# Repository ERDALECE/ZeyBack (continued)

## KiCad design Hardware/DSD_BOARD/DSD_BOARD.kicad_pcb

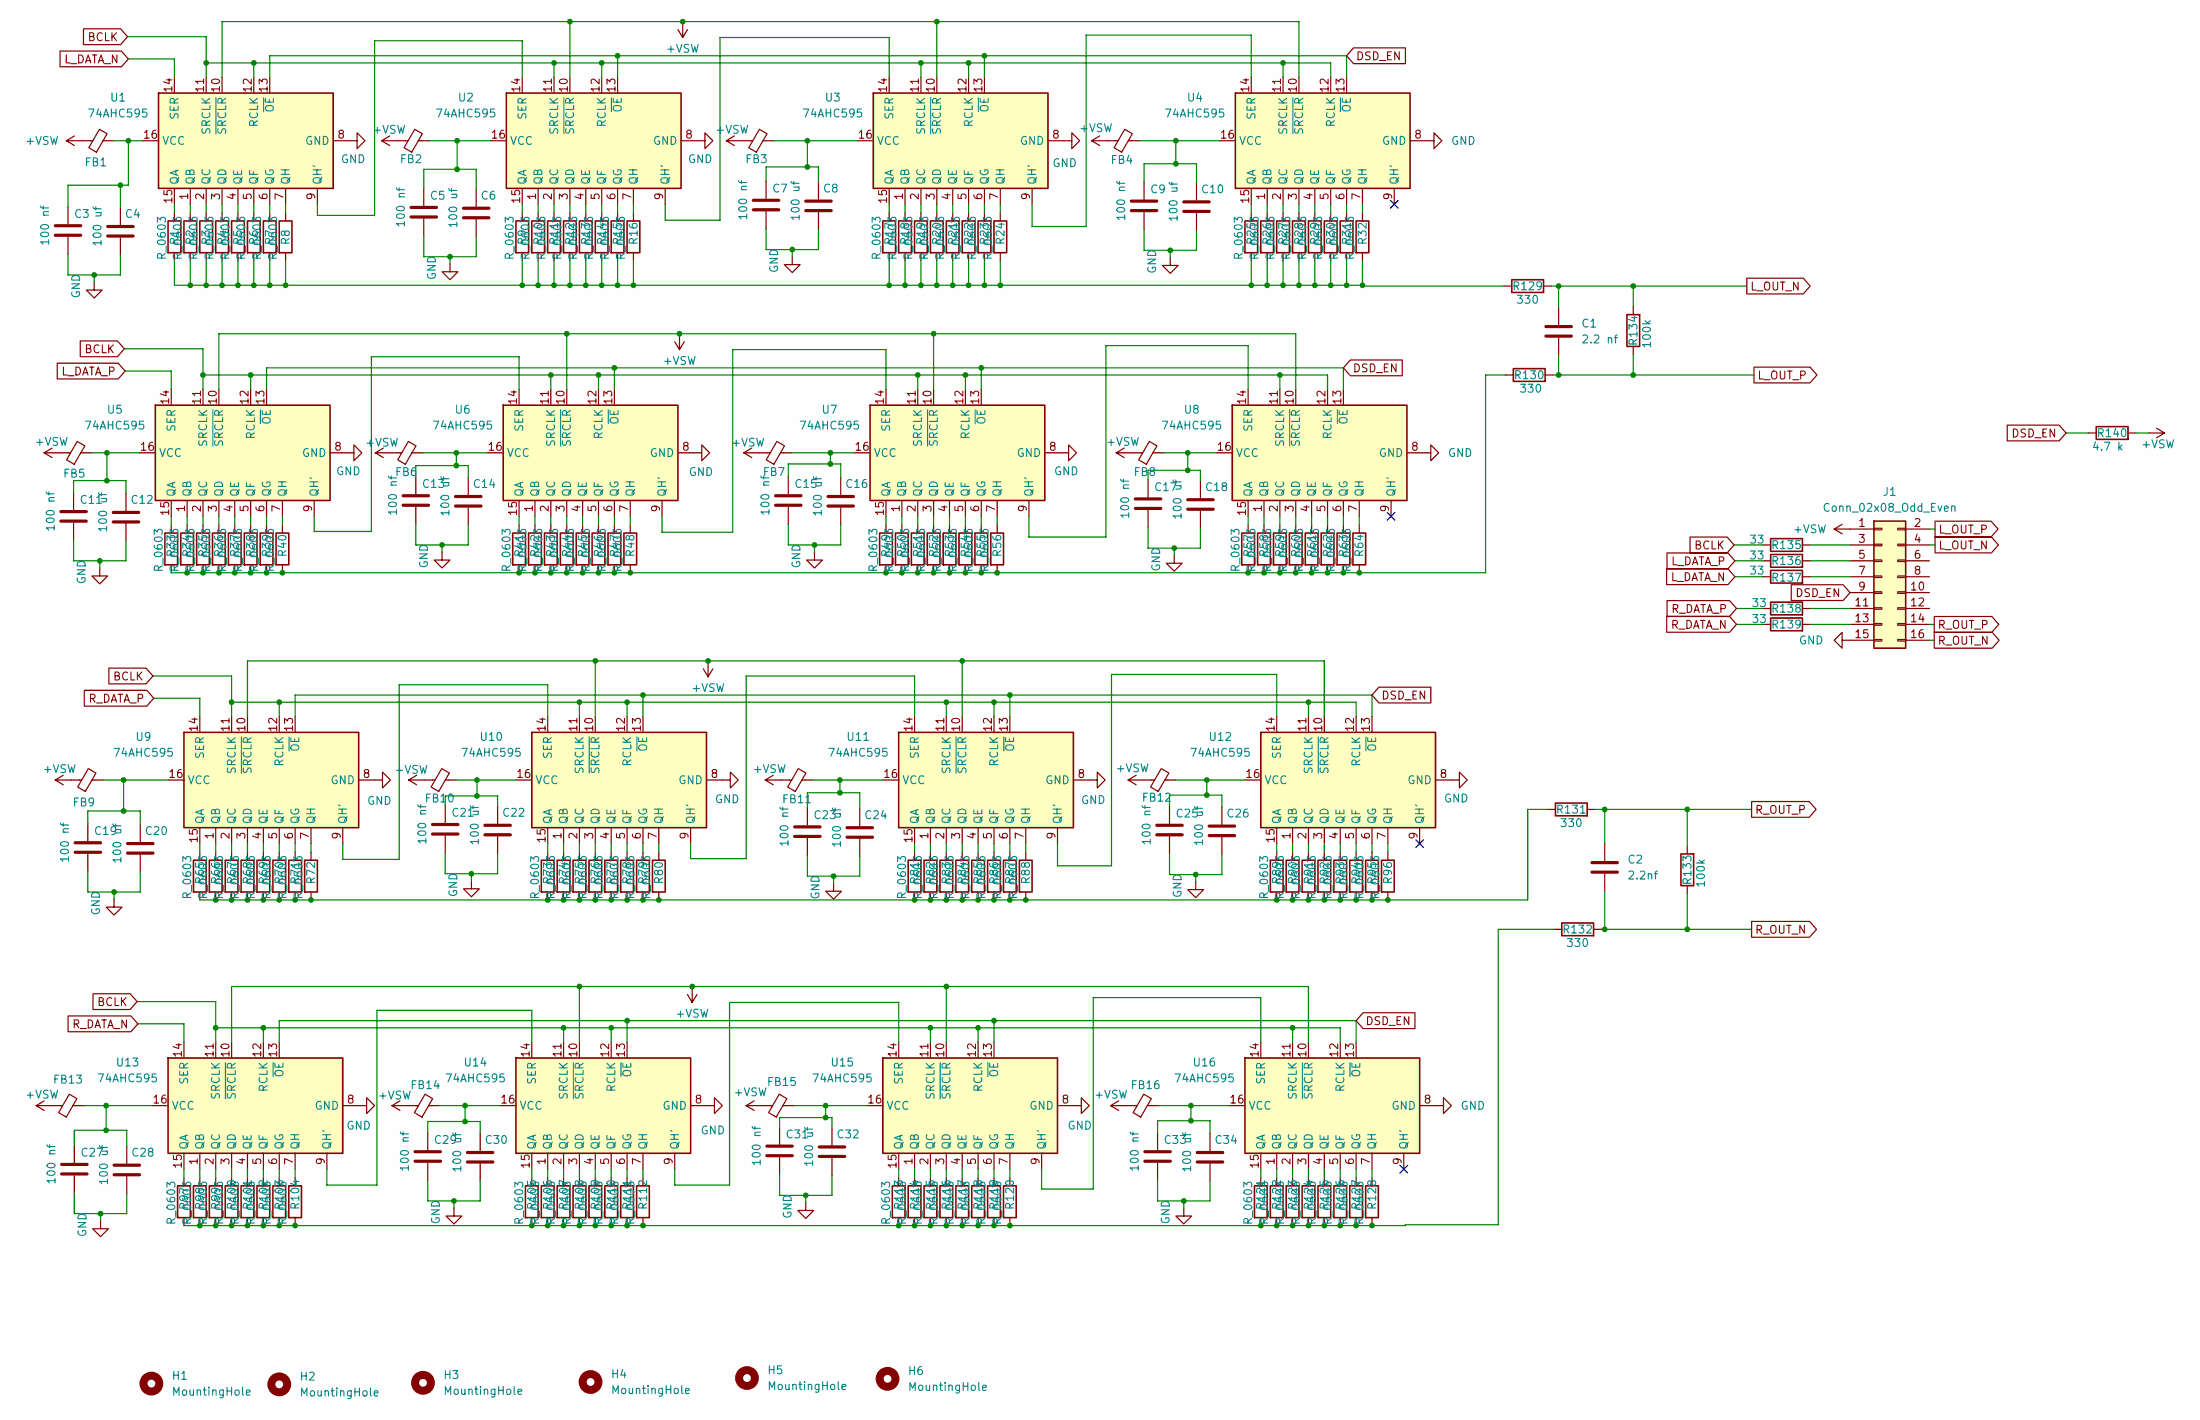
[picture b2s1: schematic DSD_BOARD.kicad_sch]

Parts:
C1: 2.2 nf; C_0603_1608Metric
C2: 2.2nf; C_0603_1608Metric
C3, C5, C7, C9, C11, C13, C15, C17, C19, C21, C23, C25, C27, C29, C31, C33: 100 nf; C_0603_1608Metric
C4, C6, C8, C10, C12, C14, C16, C18, C20, C22, C24, C26, C28, C30, C32, C34: 100 uf; C_1210_3225Metric_Pad1.33x2.70mm
FB1, FB2, FB3, FB4, FB5, FB6, FB7, FB8, FB9, FB10, FB11, FB12, FB13, FB14, FB15, FB16: bead; R_0603_1608Metric
H1, H2, H3, H4, H5, H6: MountingHole; MountingHole_3.2mm_M3
J1: Conn_02x08_Odd_Even; PinHeader_2x08_P2.54mm_Vertical
R1, R2, R3, R4, R5, R6, R7, R8, R9, R10, R11, R12, R13, R14, R15, R16, R17, R18, R19, R20, R21, R22, R23, R24, R25, R26, R27, R28, R29, R30, R31, R32, R33, R34, R35, R36, R37, R38, R39, R40, R41, R42, R43, R44, R45, R46, R47, R48, R49, R50, R51, R52, R53, R54, R55, R56, R57, R58, R59, R60, R61, R62, R63, R64, R65, R66, R67, R68, R69, R70, R71, R72, R73, R74, R75, R76, R77, R78, R79, R80, R81, R82, R83, R84, R85, R86, R87, R88, R89, R90, R91, R92, R93, R94, R95, R96, R97, R98, R99, R100, R101, R102, R103, R104, R105, R106, R107, R108, R109, R110, R111, R112, R113, R114, R115, R116, R117, R118, R119, R120, R121, R122, R123, R124, R125, R126, R127, R128: R_0603; R_0603_1608Metric
R129, R130, R131, R132: 330; R_0603_1608Metric
R133, R134: 100k; R_0603_1608Metric
R135, R136, R137, R138, R139: 33; R_0603_1608Metric
R140: 4.7 k; R_0603_1608Metric
U1, U2, U3, U4, U5, U6, U7, U8, U9, U10, U11, U12, U13, U14, U15, U16: 74AHC595; TSSOP-16_4.4x5mm_P0.65mm

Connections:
+VSW: FB1.1, FB2.1, FB3.1, FB4.1, FB5.1, FB6.1, FB7.1, FB8.1, FB9.1, FB10.1, FB11.1, FB12.1, FB13.1, FB14.1, FB15.1, FB16.1, J1.1, R140.2, U1.10 (~SRCLR), U2.10 (~SRCLR), U3.10 (~SRCLR), U4.10 (~SRCLR), U5.10 (~SRCLR), U6.10 (~SRCLR), U7.10 (~SRCLR), U8.10 (~SRCLR), U9.10 (~SRCLR), U10.10 (~SRCLR), U11.10 (~SRCLR), U12.10 (~SRCLR), U13.10 (~SRCLR), U14.10 (~SRCLR), U15.10 (~SRCLR), U16.10 (~SRCLR)
BCLK: R135.1, U1.11 (SRCLK), U1.12 (RCLK), U2.11 (SRCLK), U2.12 (RCLK), U3.11 (SRCLK), U3.12 (RCLK), U4.11 (SRCLK), U4.12 (RCLK), U5.11 (SRCLK), U5.12 (RCLK), U6.11 (SRCLK), U6.12 (RCLK), U7.11 (SRCLK), U7.12 (RCLK), U8.11 (SRCLK), U8.12 (RCLK), U9.11 (SRCLK), U9.12 (RCLK), U10.11 (SRCLK), U10.12 (RCLK), U11.11 (SRCLK), U11.12 (RCLK), U12.11 (SRCLK), U12.12 (RCLK), U13.11 (SRCLK), U13.12 (RCLK), U14.11 (SRCLK), U14.12 (RCLK), U15.11 (SRCLK), U15.12 (RCLK), U16.11 (SRCLK), U16.12 (RCLK)
DSD_EN: J1.9, R140.1, U1.13 (~OE), U2.13 (~OE), U3.13 (~OE), U4.13 (~OE), U5.13 (~OE), U6.13 (~OE), U7.13 (~OE), U8.13 (~OE), U9.13 (~OE), U10.13 (~OE), U11.13 (~OE), U12.13 (~OE), U13.13 (~OE), U14.13 (~OE), U15.13 (~OE), U16.13 (~OE)
GND: C3.2, C4.2, C5.2, C6.2, C7.2, C8.2, C9.2, C10.2, C11.2, C12.2, C13.2, C14.2, C15.2, C16.2, C17.2, C18.2, C19.2, C20.2, C21.2, C22.2, C23.2, C24.2, C25.2, C26.2, C27.2, C28.2, C29.2, C30.2, C31.2, C32.2, C33.2, C34.2, J1.15, U1.8 (GND), U2.8 (GND), U3.8 (GND), U4.8 (GND), U5.8 (GND), U6.8 (GND), U7.8 (GND), U8.8 (GND), U9.8 (GND), U10.8 (GND), U11.8 (GND), U12.8 (GND), U13.8 (GND), U14.8 (GND), U15.8 (GND), U16.8 (GND)
L_DATA_N: R137.1, U1.14 (SER)
L_DATA_P: R136.1, U5.14 (SER)
L_OUT_N: C1.1, J1.4, R129.2, R134.2
L_OUT_P: C1.2, J1.2, R130.2, R134.1
unnamed: J1.3, R135.2
unnamed: J1.5, R136.2
unnamed: J1.7, R137.2
unnamed: J1.11, R138.2
unnamed: J1.13, R139.2
unnamed: R1.2, R2.2, R3.2, R4.2, R5.2, R6.2, R7.2, R8.2, R9.2, R10.2, R11.2, R12.2, R13.2, R14.2, R15.2, R16.2, R17.2, R18.2, R19.2, R20.2, R21.2, R22.2, R23.2, R24.2, R25.2, R26.2, R27.2, R28.2, R29.2, R30.2, R31.2, R32.2, R129.1
unnamed: R97.2, R98.2, R99.2, R100.2, R101.2, R102.2, R103.2, R104.2, R105.2, R106.2, R107.2, R108.2, R109.2, R110.2, R111.2, R112.2, R113.2, R114.2, R115.2, R116.2, R117.2, R118.2, R119.2, R120.2, R121.2, R122.2, R123.2, R124.2, R125.2, R126.2, R127.2, R128.2, R132.1
unnamed: R33.2, R34.2, R35.2, R36.2, R37.2, R38.2, R39.2, R40.2, R41.2, R42.2, R43.2, R44.2, R45.2, R46.2, R47.2, R48.2, R49.2, R50.2, R51.2, R52.2, R53.2, R54.2, R55.2, R56.2, R57.2, R58.2, R59.2, R60.2, R61.2, R62.2, R63.2, R64.2, R130.1
unnamed: R65.2, R66.2, R67.2, R68.2, R69.2, R70.2, R71.2, R72.2, R73.2, R74.2, R75.2, R76.2, R77.2, R78.2, R79.2, R80.2, R81.2, R82.2, R83.2, R84.2, R85.2, R86.2, R87.2, R88.2, R89.2, R90.2, R91.2, R92.2, R93.2, R94.2, R95.2, R96.2, R131.1
unnamed: R1.1, U1.15 (QA)
unnamed: R2.1, U1.1 (QB)
unnamed: R3.1, U1.2 (QC)
unnamed: R4.1, U1.3 (QD)
unnamed: R5.1, U1.4 (QE)
unnamed: R6.1, U1.5 (QF)
unnamed: R7.1, U1.6 (QG)
unnamed: U1.9 (QH'), U2.14 (SER)
unnamed: R8.1, U1.7 (QH)
unnamed: C3.1, C4.1, FB1.2, U1.16 (VCC)
unnamed: R9.1, U2.15 (QA)
unnamed: R10.1, U2.1 (QB)
unnamed: R11.1, U2.2 (QC)
unnamed: R12.1, U2.3 (QD)
unnamed: R13.1, U2.4 (QE)
unnamed: R14.1, U2.5 (QF)
unnamed: R15.1, U2.6 (QG)
unnamed: U2.9 (QH'), U3.14 (SER)
unnamed: R16.1, U2.7 (QH)
unnamed: C5.1, C6.1, FB2.2, U2.16 (VCC)
unnamed: R17.1, U3.15 (QA)
unnamed: R18.1, U3.1 (QB)
unnamed: R19.1, U3.2 (QC)
unnamed: R20.1, U3.3 (QD)
unnamed: R21.1, U3.4 (QE)
unnamed: R22.1, U3.5 (QF)
unnamed: R23.1, U3.6 (QG)
unnamed: U3.9 (QH'), U4.14 (SER)
unnamed: R24.1, U3.7 (QH)
unnamed: C7.1, C8.1, FB3.2, U3.16 (VCC)
unnamed: R25.1, U4.15 (QA)
unnamed: R26.1, U4.1 (QB)
unnamed: R27.1, U4.2 (QC)
unnamed: R28.1, U4.3 (QD)
unnamed: R29.1, U4.4 (QE)
unnamed: R30.1, U4.5 (QF)
unnamed: R31.1, U4.6 (QG)
unnamed: R32.1, U4.7 (QH)
unnamed: C9.1, C10.1, FB4.2, U4.16 (VCC)
unnamed: R33.1, U5.15 (QA)
unnamed: R34.1, U5.1 (QB)
unnamed: R35.1, U5.2 (QC)
unnamed: R36.1, U5.3 (QD)
unnamed: R37.1, U5.4 (QE)
unnamed: R38.1, U5.5 (QF)
unnamed: R39.1, U5.6 (QG)
unnamed: U5.9 (QH'), U6.14 (SER)
unnamed: R40.1, U5.7 (QH)
unnamed: C11.1, C12.1, FB5.2, U5.16 (VCC)
unnamed: R41.1, U6.15 (QA)
unnamed: R42.1, U6.1 (QB)
unnamed: R43.1, U6.2 (QC)
unnamed: R44.1, U6.3 (QD)
unnamed: R45.1, U6.4 (QE)
unnamed: R46.1, U6.5 (QF)
unnamed: R47.1, U6.6 (QG)
unnamed: U6.9 (QH'), U7.14 (SER)
unnamed: R48.1, U6.7 (QH)
unnamed: C13.1, C14.1, FB6.2, U6.16 (VCC)
unnamed: R49.1, U7.15 (QA)
unnamed: R50.1, U7.1 (QB)
unnamed: R51.1, U7.2 (QC)
unnamed: R52.1, U7.3 (QD)
unnamed: R53.1, U7.4 (QE)
unnamed: R54.1, U7.5 (QF)
unnamed: R55.1, U7.6 (QG)
unnamed: U7.9 (QH'), U8.14 (SER)
unnamed: R56.1, U7.7 (QH)
unnamed: C15.1, C16.1, FB7.2, U7.16 (VCC)
unnamed: R57.1, U8.15 (QA)
unnamed: R58.1, U8.1 (QB)
unnamed: R59.1, U8.2 (QC)
unnamed: R60.1, U8.3 (QD)
unnamed: R61.1, U8.4 (QE)
unnamed: R62.1, U8.5 (QF)
unnamed: R63.1, U8.6 (QG)
unnamed: R64.1, U8.7 (QH)
unnamed: C17.1, C18.1, FB8.2, U8.16 (VCC)
unnamed: R65.1, U9.15 (QA)
unnamed: R66.1, U9.1 (QB)
unnamed: R67.1, U9.2 (QC)
unnamed: R68.1, U9.3 (QD)
unnamed: R69.1, U9.4 (QE)
unnamed: R70.1, U9.5 (QF)
unnamed: R71.1, U9.6 (QG)
unnamed: R72.1, U9.7 (QH)
unnamed: C19.1, C20.1, FB9.2, U9.16 (VCC)
unnamed: R73.1, U10.15 (QA)
unnamed: R74.1, U10.1 (QB)
unnamed: R75.1, U10.2 (QC)
unnamed: R76.1, U10.3 (QD)
unnamed: R77.1, U10.4 (QE)
unnamed: R78.1, U10.5 (QF)
unnamed: R79.1, U10.6 (QG)
unnamed: U10.9 (QH'), U11.14 (SER)
unnamed: R80.1, U10.7 (QH)
unnamed: U9.9 (QH'), U10.14 (SER)
unnamed: C21.1, C22.1, FB10.2, U10.16 (VCC)
unnamed: R81.1, U11.15 (QA)
unnamed: R82.1, U11.1 (QB)
unnamed: R83.1, U11.2 (QC)
unnamed: R84.1, U11.3 (QD)
unnamed: R85.1, U11.4 (QE)
unnamed: R86.1, U11.5 (QF)
unnamed: R87.1, U11.6 (QG)
unnamed: U11.9 (QH'), U12.14 (SER)
unnamed: R88.1, U11.7 (QH)
unnamed: C23.1, C24.1, FB11.2, U11.16 (VCC)
unnamed: R89.1, U12.15 (QA)
unnamed: R90.1, U12.1 (QB)
unnamed: R91.1, U12.2 (QC)
unnamed: R92.1, U12.3 (QD)
unnamed: R93.1, U12.4 (QE)
unnamed: R94.1, U12.5 (QF)
unnamed: R95.1, U12.6 (QG)
unnamed: R96.1, U12.7 (QH)
unnamed: C25.1, C26.1, FB12.2, U12.16 (VCC)
unnamed: R97.1, U13.15 (QA)
unnamed: R98.1, U13.1 (QB)
unnamed: R99.1, U13.2 (QC)
unnamed: R100.1, U13.3 (QD)
unnamed: R101.1, U13.4 (QE)
unnamed: R102.1, U13.5 (QF)
unnamed: R103.1, U13.6 (QG)
unnamed: U13.9 (QH'), U14.14 (SER)
unnamed: R104.1, U13.7 (QH)
unnamed: C27.1, C28.1, FB13.2, U13.16 (VCC)
unnamed: R105.1, U14.15 (QA)
unnamed: R106.1, U14.1 (QB)
unnamed: R107.1, U14.2 (QC)
unnamed: R108.1, U14.3 (QD)
unnamed: R109.1, U14.4 (QE)
unnamed: R110.1, U14.5 (QF)
unnamed: R111.1, U14.6 (QG)
unnamed: U14.9 (QH'), U15.14 (SER)
unnamed: R112.1, U14.7 (QH)
unnamed: C29.1, C30.1, FB14.2, U14.16 (VCC)
unnamed: R113.1, U15.15 (QA)
unnamed: R114.1, U15.1 (QB)
unnamed: R115.1, U15.2 (QC)
unnamed: R116.1, U15.3 (QD)
unnamed: R117.1, U15.4 (QE)
unnamed: R118.1, U15.5 (QF)
unnamed: R119.1, U15.6 (QG)
unnamed: U15.9 (QH'), U16.14 (SER)
unnamed: R120.1, U15.7 (QH)
unnamed: C31.1, C32.1, FB15.2, U15.16 (VCC)
unnamed: R121.1, U16.15 (QA)
unnamed: R122.1, U16.1 (QB)
unnamed: R123.1, U16.2 (QC)
unnamed: R124.1, U16.3 (QD)
unnamed: R125.1, U16.4 (QE)
unnamed: R126.1, U16.5 (QF)
unnamed: R127.1, U16.6 (QG)
unnamed: R128.1, U16.7 (QH)
unnamed: C33.1, C34.1, FB16.2, U16.16 (VCC)
R_DATA_N: R139.1, U13.14 (SER)
R_DATA_P: R138.1, U9.14 (SER)
R_OUT_N: C2.2, J1.16, R132.2, R133.1
R_OUT_P: C2.1, J1.14, R131.2, R133.2

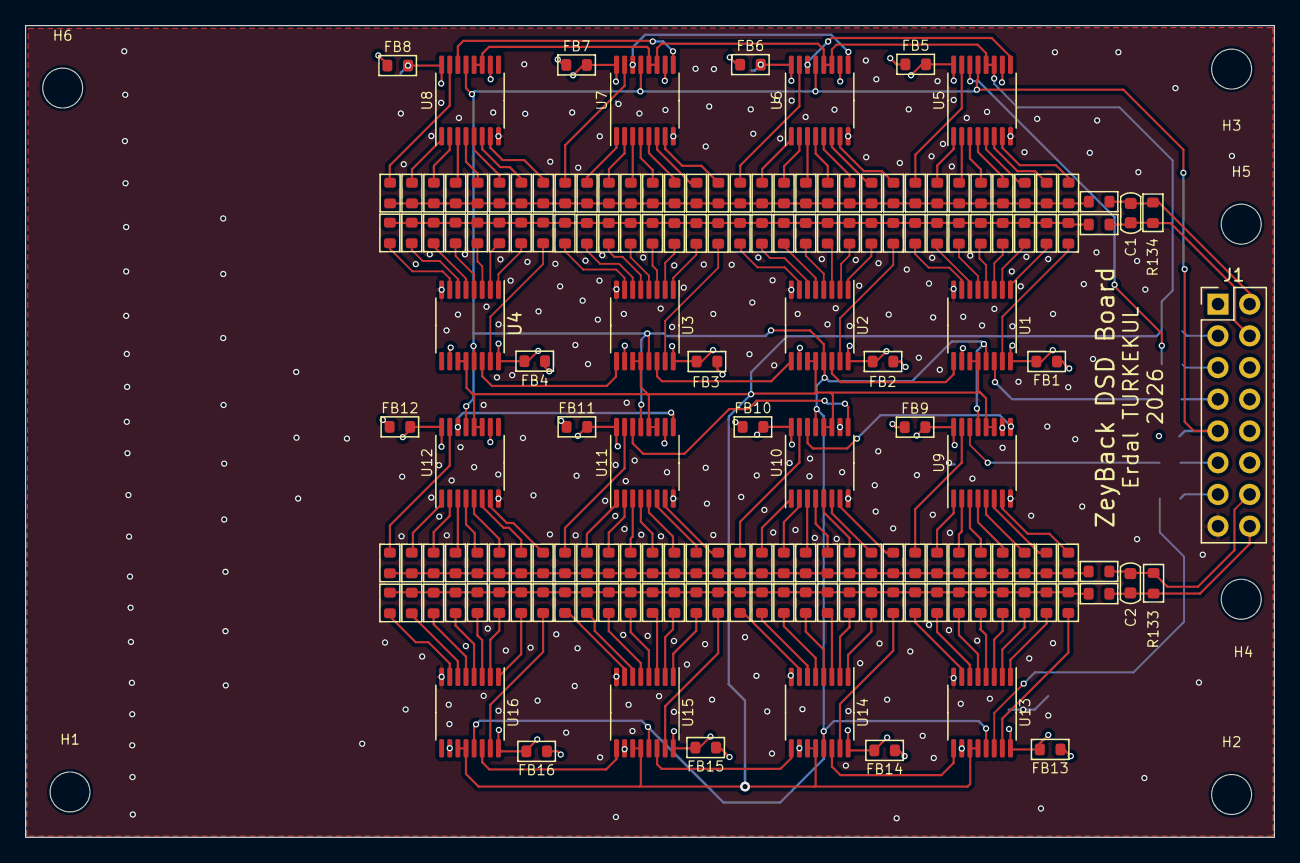
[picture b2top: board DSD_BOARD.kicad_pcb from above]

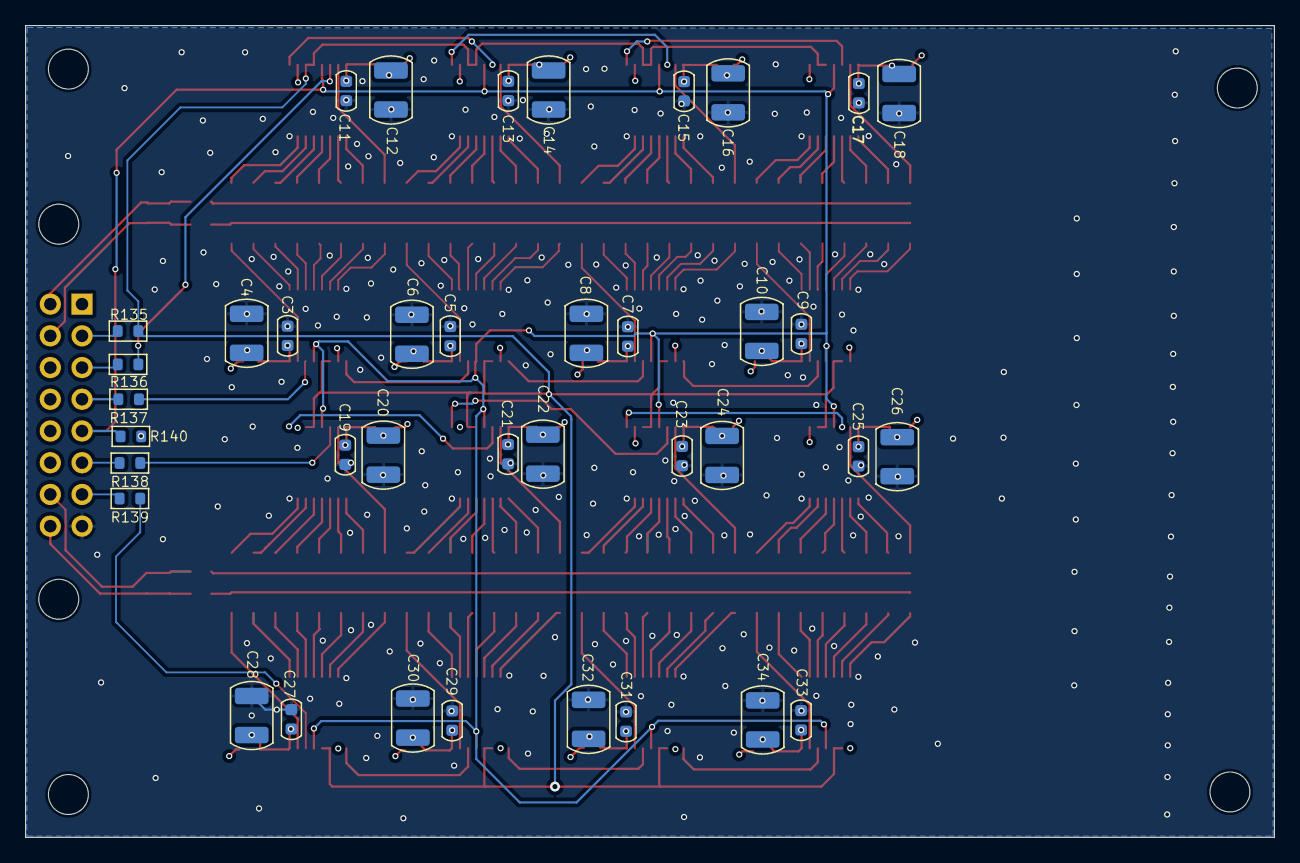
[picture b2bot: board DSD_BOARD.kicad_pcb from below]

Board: 4 copper layers, 100.0 x 65.0 mm, 213 parts (38 on the bottom side), 177 nets.

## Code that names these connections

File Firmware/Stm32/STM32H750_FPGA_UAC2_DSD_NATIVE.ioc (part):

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Mcu.Name=STM32H750XBHx
Mcu.Package=TFBGA240
Mcu.UserName=STM32H750XBHx
PA0.GPIOParameters=GPIO_Speed,PinState,GPIO_PuPd,GPIO_Label
PA0.GPIO_Label=USB_RST
PA0.GPIO_PuPd=GPIO_NOPULL
PA0.GPIO_Speed=GPIO_SPEED_FREQ_MEDIUM
PA0.PinState=GPIO_PIN_SET
PA0.Signal=GPIO_Output
PA1.GPIOParameters=GPIO_Label
PA1.GPIO_Label=LED2
PA1.Signal=GPIO_Output
PA10.GPIOParameters=GPIO_Speed,PinState,GPIO_Label
PA10.GPIO_Label=RST_SI
PA10.GPIO_Speed=GPIO_SPEED_FREQ_MEDIUM
PA10.PinState=GPIO_PIN_SET
PA10.Signal=GPIO_Output
PA12.GPIOParameters=GPIO_Label
PA12.GPIO_Label=OLED_CLK
PA12.Mode=Simplex_Bidirectional_Master
PA12.Signal=SPI2_SCK
PA15\ (JTDI).Signal=S_TIM2_CH1_ETR
PA3.Mode=Device_HS
PA3.Signal=USB_OTG_HS_ULPI_D0
PA4.GPIOParameters=GPIO_Label
PA4.GPIO_Label=LED1
PA4.Signal=GPIO_Output
PA5.Mode=Device_HS
PA5.Signal=USB_OTG_HS_ULPI_CK
PA8.Mode=Clock-out-1
PA8.Signal=RCC_MCO_1
PA9.GPIOParameters=GPIO_PuPd,GPIO_Label
PA9.GPIO_Label=STM32_SYNC
PA9.GPIO_PuPd=GPIO_PULLUP
PA9.Signal=GPIO_Input
PB0.Mode=Device_HS
PB0.Signal=USB_OTG_HS_ULPI_D1
PB1.Mode=Device_HS
PB1.Signal=USB_OTG_HS_ULPI_D2
PB10.GPIOParameters=PinAttribute
PB10.Mode=Device_HS
PB10.PinAttribute=Free
PB10.Signal=USB_OTG_HS_ULPI_D3
PB11.GPIOParameters=PinAttribute
PB11.Mode=Device_HS
PB11.PinAttribute=Free
PB11.Signal=USB_OTG_HS_ULPI_D4
PB12.Mode=Device_HS
PB12.Signal=USB_OTG_HS_ULPI_D5
PB13.Mode=Device_HS
PB13.Signal=USB_OTG_HS_ULPI_D6
PB14.GPIOParameters=GPIO_Label
PB14.GPIO_Label=OLED_CS
PB14.Signal=GPIO_Output
PB15.GPIOParameters=GPIO_Label
PB15.GPIO_Label=OLED_DATA
PB15.Mode=Simplex_Bidirectional_Master
PB15.Signal=SPI2_MOSI
PB5.Mode=Device_HS
PB5.Signal=USB_OTG_HS_ULPI_D7
PB6.Mode=I2C
PB6.Signal=I2C1_SCL
PB7.Mode=I2C
PB7.Signal=I2C1_SDA
PC0.GPIOParameters=PinAttribute
PC0.Mode=Device_HS
PC0.PinAttribute=Free
PC0.Signal=USB_OTG_HS_ULPI_STP
PC10.Mode=Asynchronous
PC10.Signal=UART4_TX
PC11.Mode=Asynchronous
PC11.Signal=UART4_RX
PC15-OSC32_OUT\ (OSC32_OUT).GPIOParameters=GPIO_Label
PC15-OSC32_OUT\ (OSC32_OUT).GPIO_Label=RSTB
PC15-OSC32_OUT\ (OSC32_OUT).Signal=GPIO_Output
PC3.GPIOParameters=PinAttribute
PC3.Mode=Device_HS
PC3.PinAttribute=Free
PC3.Signal=USB_OTG_HS_ULPI_NXT
PC4.GPIOParameters=GPIO_Label
PC4.GPIO_Label=LED3
PC4.Signal=GPIO_Output
PC5.GPIOParameters=GPIO_Label
PC5.GPIO_Label=LED4
PC5.Signal=GPIO_Output
PC8.GPIOParameters=GPIO_PuPd,GPIO_Label
PC8.GPIO_Label=STM32_EN
PC8.GPIO_PuPd=GPIO_PULLUP
PC8.Signal=GPIO_Output
PC9.GPIOParameters=GPIO_PuPd,GPIO_Label
PC9.GPIO_Label=STM32_REQ
PC9.GPIO_PuPd=GPIO_PULLUP
PC9.Signal=GPIO_Input
PD0.Signal=FMC_D2_DA2
PD1.Signal=FMC_D3_DA3
PD10.Signal=FMC_D15_DA15
PD14.Signal=FMC_D0_DA0
PD15.Signal=FMC_D1_DA1
PD2.GPIOParameters=GPIO_Label
PD2.GPIO_Label=DSP
PD2.Signal=GPIO_Output
PD3.GPIOParameters=GPIO_Label
PD3.GPIO_Label=DSD_EN
PD3.Signal=GPIO_Output
PD4.GPIOParameters=GPIO_PuPd
PD4.GPIO_PuPd=GPIO_PULLUP
PD4.Signal=FMC_NOE
PD5.GPIOParameters=GPIO_PuPd
PD5.GPIO_PuPd=GPIO_PULLUP
PD5.Signal=FMC_NWE
PD6.GPIOParameters=GPIO_PuPd
PD6.GPIO_PuPd=GPIO_PULLUP
PD6.Signal=FMC_NWAIT
PD7.Mode=NorPsramChipSelect1_1
PD7.Signal=FMC_NE1
PD8.Signal=FMC_D13_DA13
PD9.Signal=FMC_D14_DA14
PE10.GPIOParameters=PinAttribute
PE10.PinAttribute=Free
PE10.Signal=FMC_D7_DA7
PE11.GPIOParameters=PinAttribute
PE11.PinAttribute=Free
PE11.Signal=FMC_D8_DA8
PE12.Signal=FMC_D9_DA9
PE13.Signal=FMC_D10_DA10
PE14.Signal=FMC_D11_DA11
PE15.Signal=FMC_D12_DA12
PE2.Mode=Full_Duplex_Master
PE2.Signal=SPI4_SCK
PE4.GPIOParameters=GPIO_Label
PE4.GPIO_Label=CS8416_CSB
PE4.Signal=GPIO_Output
PE5.Mode=Full_Duplex_Master
PE5.Signal=SPI4_MISO
PE6.Mode=Full_Duplex_Master
PE6.Signal=SPI4_MOSI
PE7.Signal=FMC_D4_DA4
PE8.Signal=FMC_D5_DA5
PE9.GPIOParameters=PinAttribute
PE9.PinAttribute=Free
PE9.Signal=FMC_D6_DA6
PF0.GPIOParameters=PinAttribute
PF0.PinAttribute=Free
PF0.Signal=FMC_A0
PF1.GPIOParameters=PinAttribute
PF1.PinAttribute=Free
PF1.Signal=FMC_A1
PF15.GPIOParameters=GPIO_Label
PF15.GPIO_Label=IR
PF15.Signal=GPIO_Input
PG2.GPIOParameters=GPIO_PuPd,GPIO_Label
PG2.GPIO_Label=SEL0
PG2.GPIO_PuPd=GPIO_PULLDOWN
PG2.Signal=GPIO_Output
PG3.GPIOParameters=GPIO_PuPd,GPIO_Label
PG3.GPIO_Label=SEL1
PG3.GPIO_PuPd=GPIO_PULLDOWN
PG3.Signal=GPIO_Output
PG4.GPIOParameters=GPIO_PuPd,GPIO_Label
PG4.GPIO_Label=SEL2
PG4.GPIO_PuPd=GPIO_PULLDOWN
PG4.Signal=GPIO_Output
PG5.GPIOParameters=GPIO_PuPd,GPIO_Label
PG5.GPIO_Label=SEL3
PG5.GPIO_PuPd=GPIO_PULLDOWN
PG5.Signal=GPIO_Output
PG6.GPIOParameters=GPIO_Label
PG6.GPIO_Label=RCLK_ON
PG6.Signal=GPIO_Output
PG7.GPIOParameters=GPIO_Label
PG7.GPIO_Label=MUTE
PG7.Signal=GPIO_Output
PH0-OSC_IN\ (PH0).GPIOParameters=PinAttribute
PH0-OSC_IN\ (PH0).Mode=HSE-External-Clock-Source
PH0-OSC_IN\ (PH0).PinAttribute=Free
PH0-OSC_IN\ (PH0).Signal=RCC_OSC_IN
PH10.Signal=FMC_D18
PH11.Signal=FMC_D19
PH12.Signal=FMC_D20
PH13.Signal=FMC_D21
PH14.Signal=FMC_D22
PH15.Signal=FMC_D23
PH6.GPIOParameters=GPIO_Label
PH6.GPIO_Label=OLED_RST
PH6.Signal=GPIO_Output
PH7.GPIOParameters=GPIO_Label
PH7.GPIO_Label=OLED_DC
PH7.Signal=GPIO_Output
PH8.Signal=FMC_D16
PH9.Signal=FMC_D17
PI0.Signal=FMC_D24
PI1.Signal=FMC_D25
PI10.GPIOParameters=PinAttribute
PI10.PinAttribute=Free
PI10.Signal=FMC_D31
PI11.GPIOParameters=PinAttribute
PI11.Mode=Device_HS
PI11.PinAttribute=Free
PI11.Signal=USB_OTG_HS_ULPI_DIR
PI2.Signal=FMC_D26
PI3.Signal=FMC_D27
PI4.GPIOParameters=GPIO_Label
PI4.GPIO_Label=HDMI_RESET
PI4.Signal=GPIO_Output
PI5.GPIOParameters=GPIO_Label
PI5.GPIO_Label=CSB_SI
PI5.Signal=GPIO_Output
PI6.Signal=FMC_D28
PI7.Signal=FMC_D29
PI9.Signal=FMC_D30
PJ10.GPIOParameters=GPIO_Label
PJ10.GPIO_Label=BitRate
PJ10.Signal=GPIO_Input
PJ11.GPIOParameters=GPIO_Label
PJ11.GPIO_Label=SR3
PJ11.Signal=GPIO_Input
PK0.GPIOParameters=GPIO_Label
PK0.GPIO_Label=SR0
PK0.Signal=GPIO_Input
PK1.GPIOParameters=GPIO_Label
PK1.GPIO_Label=SR1
PK1.Signal=GPIO_Input
PK2.GPIOParameters=GPIO_Label
PK2.GPIO_Label=SR2
PK2.Signal=GPIO_Input
RCC.HSE_VALUE=48000000
RCC.SYSCLKFreq_VALUE=480000000
RCC.SYSCLKSource=RCC_SYSCLKSOURCE_PLLCLK
board=custom

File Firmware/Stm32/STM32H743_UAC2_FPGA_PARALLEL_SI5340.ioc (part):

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Mcu.Name=STM32H743VITx
Mcu.Package=LQFP100
Mcu.UserName=STM32H743VITx
PA0.GPIOParameters=GPIO_Label
PA0.GPIO_Label=F1
PA0.Signal=GPIO_Input
PA1.GPIOParameters=GPIO_Label
PA1.GPIO_Label=F2
PA1.Signal=GPIO_Input
PA10.GPIOParameters=GPIO_Speed,PinState,GPIO_PuPd,GPIO_Label
PA10.GPIO_Label=RST_SI
PA10.GPIO_PuPd=GPIO_PULLDOWN
PA10.GPIO_Speed=GPIO_SPEED_FREQ_MEDIUM
PA10.PinState=GPIO_PIN_RESET
PA10.Signal=GPIO_Output
PA11.GPIOParameters=GPIO_Label
PA11.GPIO_Label=RCLK_ON
PA11.Signal=GPIO_Output
PA12.GPIOParameters=GPIO_Label
PA12.GPIO_Label=HDMI_RESET
PA12.Signal=GPIO_Output
PA13\ (JTMS/SWDIO).Mode=Serial_Wire
PA13\ (JTMS/SWDIO).Signal=DEBUG_JTMS-SWDIO
PA14\ (JTCK/SWCLK).Mode=Serial_Wire
PA14\ (JTCK/SWCLK).Signal=DEBUG_JTCK-SWCLK
PA2.GPIOParameters=GPIO_Label
PA2.GPIO_Label=F3
PA2.Signal=GPIO_Input
PA3.GPIOParameters=GPIO_Speed_Only_High
PA3.GPIO_Speed_Only_High=GPIO_SPEED_FREQ_VERY_HIGH
PA3.Mode=Device_HS
PA3.Signal=USB_OTG_HS_ULPI_D0
PA5.GPIOParameters=GPIO_Speed_Only_High
PA5.GPIO_Speed_Only_High=GPIO_SPEED_FREQ_VERY_HIGH
PA5.Mode=Device_HS
PA5.Signal=USB_OTG_HS_ULPI_CK
PA6.Signal=GPIO_Output
PA7.Signal=GPIO_Input
PA8.GPIOParameters=GPIO_Speed,GPIO_PuPd
PA8.GPIO_PuPd=GPIO_PULLUP
PA8.GPIO_Speed=GPIO_SPEED_FREQ_VERY_HIGH
PA8.Mode=Clock-out-1
PA8.Signal=RCC_MCO_1
PA9.GPIOParameters=GPIO_Speed,GPIO_PuPd
PA9.GPIO_PuPd=GPIO_NOPULL
PA9.GPIO_Speed=GPIO_SPEED_FREQ_LOW
PA9.Mode=Full_Duplex_Master
PA9.Signal=SPI2_SCK
PB0.GPIOParameters=GPIO_Speed_Only_High
PB0.GPIO_Speed_Only_High=GPIO_SPEED_FREQ_VERY_HIGH
PB0.Mode=Device_HS
PB0.Signal=USB_OTG_HS_ULPI_D1
PB1.GPIOParameters=GPIO_Speed_Only_High
PB1.GPIO_Speed_Only_High=GPIO_SPEED_FREQ_VERY_HIGH
PB1.Mode=Device_HS
PB1.Signal=USB_OTG_HS_ULPI_D2
PB10.GPIOParameters=GPIO_Speed_Only_High
PB10.GPIO_Speed_Only_High=GPIO_SPEED_FREQ_VERY_HIGH
PB10.Mode=Device_HS
PB10.Signal=USB_OTG_HS_ULPI_D3
PB11.GPIOParameters=GPIO_Speed_Only_High
PB11.GPIO_Speed_Only_High=GPIO_SPEED_FREQ_VERY_HIGH
PB11.Mode=Device_HS
PB11.Signal=USB_OTG_HS_ULPI_D4
PB12.GPIOParameters=GPIO_Speed_Only_High
PB12.GPIO_Speed_Only_High=GPIO_SPEED_FREQ_VERY_HIGH
PB12.Mode=Device_HS
PB12.Signal=USB_OTG_HS_ULPI_D5
PB13.GPIOParameters=GPIO_Speed_Only_High
PB13.GPIO_Speed_Only_High=GPIO_SPEED_FREQ_VERY_HIGH
PB13.Mode=Device_HS
PB13.Signal=USB_OTG_HS_ULPI_D6
PB14.GPIOParameters=GPIO_Speed,GPIO_PuPd
PB14.GPIO_PuPd=GPIO_NOPULL
PB14.GPIO_Speed=GPIO_SPEED_FREQ_LOW
PB14.Mode=Full_Duplex_Master
PB14.Signal=SPI2_MISO
PB15.GPIOParameters=GPIO_Speed,GPIO_PuPd
PB15.GPIO_PuPd=GPIO_PULLDOWN
PB15.GPIO_Speed=GPIO_SPEED_FREQ_LOW
PB15.Mode=Full_Duplex_Master
PB15.Signal=SPI2_MOSI
PB2.Signal=GPIO_Output
PB3\ (JTDO/TRACESWO).Signal=GPIO_Output
PB4\ (NJTRST).GPIOParameters=GPIO_Label
PB4\ (NJTRST).GPIO_Label=BitRate
PB4\ (NJTRST).Signal=GPIO_Input
PB5.GPIOParameters=GPIO_Speed_Only_High
PB5.GPIO_Speed_Only_High=GPIO_SPEED_FREQ_VERY_HIGH
PB5.Mode=Device_HS
PB5.Signal=USB_OTG_HS_ULPI_D7
PB6.Mode=I2C
PB6.Signal=I2C1_SCL
PB7.Mode=I2C
PB7.Signal=I2C1_SDA
PB8.Signal=GPIO_Input
PB9.Signal=GPIO_Input
PC0.GPIOParameters=GPIO_Speed_Only_High
PC0.GPIO_Speed_Only_High=GPIO_SPEED_FREQ_VERY_HIGH
PC0.Mode=Device_HS
PC0.Signal=USB_OTG_HS_ULPI_STP
PC10.Signal=GPIO_Input
PC11.GPIOParameters=GPIO_Label
PC11.GPIO_Label=HDMI_INT
PC11.Signal=GPIO_Input
PC12.GPIOParameters=GPIO_Label
PC12.GPIO_Label=DSP
PC12.Signal=GPIO_Output
PC13.GPIOParameters=GPIO_Label
PC13.GPIO_Label=SEL1
PC13.Signal=GPIO_Output
PC14-OSC32_IN\ (OSC32_IN).GPIOParameters=GPIO_PuPd,GPIO_Label
PC14-OSC32_IN\ (OSC32_IN).GPIO_Label=SEL0
PC14-OSC32_IN\ (OSC32_IN).GPIO_PuPd=GPIO_PULLDOWN
PC14-OSC32_IN\ (OSC32_IN).Signal=GPIO_Output
PC15-OSC32_OUT\ (OSC32_OUT).GPIOParameters=GPIO_Label
PC15-OSC32_OUT\ (OSC32_OUT).GPIO_Label=F0
PC15-OSC32_OUT\ (OSC32_OUT).Signal=GPIO_Input
PC2_C.GPIOParameters=GPIO_Speed_Only_High
PC2_C.GPIO_Speed_Only_High=GPIO_SPEED_FREQ_VERY_HIGH
PC2_C.Mode=Device_HS
PC2_C.Signal=USB_OTG_HS_ULPI_DIR
PC3_C.GPIOParameters=GPIO_Speed_Only_High
PC3_C.GPIO_Speed_Only_High=GPIO_SPEED_FREQ_VERY_HIGH
PC3_C.Mode=Device_HS
PC3_C.Signal=USB_OTG_HS_ULPI_NXT
PC6.GPIOParameters=GPIO_Speed,GPIO_Label
PC6.GPIO_Label=VALID
PC6.GPIO_Speed=GPIO_SPEED_FREQ_HIGH
PC6.Signal=GPIO_Output
PC7.GPIOParameters=GPIO_Speed,GPIO_Label
PC7.GPIO_Label=CLK
PC7.GPIO_Speed=GPIO_SPEED_FREQ_HIGH
PC7.Signal=GPIO_Output
PC8.GPIOParameters=GPIO_Label
PC8.GPIO_Label=SEL2
PC8.Signal=GPIO_Output
PC9.GPIOParameters=GPIO_Speed,PinState,GPIO_PuPd,GPIO_Label
PC9.GPIO_Label=CSB_SI
PC9.GPIO_PuPd=GPIO_NOPULL
PC9.GPIO_Speed=GPIO_SPEED_FREQ_MEDIUM
PC9.PinState=GPIO_PIN_SET
PC9.Signal=GPIO_Output
PD0.Signal=GPIO_Output
PD1.GPIOParameters=GPIO_Label
PD1.GPIO_Label=CS8416_CSB
PD1.Signal=GPIO_Output
PD10.GPIOParameters=GPIO_Speed
PD10.GPIO_Speed=GPIO_SPEED_FREQ_VERY_HIGH
PD10.Signal=GPIO_Output
PD11.GPIOParameters=GPIO_Speed
PD11.GPIO_Speed=GPIO_SPEED_FREQ_VERY_HIGH
PD11.Signal=GPIO_Output
PD12.GPIOParameters=GPIO_Speed
PD12.GPIO_Speed=GPIO_SPEED_FREQ_VERY_HIGH
PD12.Signal=GPIO_Output
PD13.GPIOParameters=GPIO_Speed
PD13.GPIO_Speed=GPIO_SPEED_FREQ_VERY_HIGH
PD13.Signal=GPIO_Output
PD14.GPIOParameters=GPIO_Speed
PD14.GPIO_Speed=GPIO_SPEED_FREQ_VERY_HIGH
PD14.Signal=GPIO_Output
PD15.GPIOParameters=GPIO_Speed
PD15.GPIO_Speed=GPIO_SPEED_FREQ_VERY_HIGH
PD15.Signal=GPIO_Output
PD2.Signal=GPIO_Output
PD3.GPIOParameters=GPIO_Speed,PinState
PD3.GPIO_Speed=GPIO_SPEED_FREQ_VERY_HIGH
PD3.PinState=GPIO_PIN_RESET
PD3.Signal=GPIO_Output
PD4.GPIOParameters=GPIO_Speed
PD4.GPIO_Speed=GPIO_SPEED_FREQ_VERY_HIGH
PD4.Signal=GPIO_Output
PD5.GPIOParameters=GPIO_Speed
PD5.GPIO_Speed=GPIO_SPEED_FREQ_VERY_HIGH
PD5.Signal=GPIO_Output
PD6.Signal=GPIO_Input
PD7.GPIOParameters=PinState,GPIO_PuPd,GPIO_Label
PD7.GPIO_Label=RSTB
PD7.GPIO_PuPd=GPIO_PULLUP
PD7.PinState=GPIO_PIN_RESET
PD7.Signal=GPIO_Output
PD8.GPIOParameters=GPIO_Speed
PD8.GPIO_Speed=GPIO_SPEED_FREQ_VERY_HIGH
PD8.Signal=GPIO_Output
PD9.GPIOParameters=GPIO_Speed
PD9.GPIO_Speed=GPIO_SPEED_FREQ_VERY_HIGH
PD9.Signal=GPIO_Output
PE0.GPIOParameters=GPIO_Speed,PinState,GPIO_PuPd,GPIO_Label
PE0.GPIO_Label=USB_RST
PE0.GPIO_PuPd=GPIO_PULLUP
PE0.GPIO_Speed=GPIO_SPEED_FREQ_HIGH
PE0.PinState=GPIO_PIN_SET
PE0.Signal=GPIO_Output
PE1.GPIOParameters=GPIO_Label
PE1.GPIO_Label=LED1
PE1.Signal=GPIO_Output
PE10.GPIOParameters=GPIO_PuPd,GPIO_Label,GPIO_ModeDefaultEXTI
PE10.GPIO_Label=IR
PE10.GPIO_ModeDefaultEXTI=GPIO_MODE_IT_FALLING
PE10.GPIO_PuPd=GPIO_PULLDOWN
PE10.Signal=GPXTI10
PE11.GPIOParameters=GPIO_Speed,GPIO_PuPd,GPIO_Label
PE11.GPIO_Label=OLED_CS
PE11.GPIO_PuPd=GPIO_PULLUP
PE11.GPIO_Speed=GPIO_SPEED_FREQ_VERY_HIGH
PE11.Signal=GPIO_Output
PE12.GPIOParameters=GPIO_Speed,GPIO_PuPd,GPIO_Label
PE12.GPIO_Label=OLED_CLK
PE12.GPIO_PuPd=GPIO_PULLUP
PE12.GPIO_Speed=GPIO_SPEED_FREQ_VERY_HIGH
PE12.Mode=TX_Only_Simplex_Unidirect_Master
PE12.Signal=SPI4_SCK
PE13.GPIOParameters=GPIO_Speed,GPIO_PuPd,GPIO_Label
PE13.GPIO_Label=OLED_DC
PE13.GPIO_PuPd=GPIO_PULLUP
PE13.GPIO_Speed=GPIO_SPEED_FREQ_VERY_HIGH
PE13.Signal=GPIO_Output
PE14.GPIOParameters=GPIO_Speed,GPIO_PuPd,GPIO_Label
PE14.GPIO_Label=OLED_DATA
PE14.GPIO_PuPd=GPIO_PULLUP
PE14.GPIO_Speed=GPIO_SPEED_FREQ_VERY_HIGH
PE14.Mode=TX_Only_Simplex_Unidirect_Master
PE14.Signal=SPI4_MOSI
PE15.GPIOParameters=GPIO_Speed,GPIO_PuPd,GPIO_Label
PE15.GPIO_Label=OLED_RST
PE15.GPIO_PuPd=GPIO_PULLUP
PE15.GPIO_Speed=GPIO_SPEED_FREQ_VERY_HIGH
PE15.Signal=GPIO_Output
PE2.GPIOParameters=GPIO_Label
PE2.GPIO_Label=LED2
PE2.Signal=GPIO_Output
PE3.GPIOParameters=GPIO_Label
PE3.GPIO_Label=LED3
PE3.Signal=GPIO_Output
PE4.GPIOParameters=GPIO_Label
PE4.GPIO_Label=LED4
PE4.Signal=GPIO_Output
PE6.GPIOParameters=GPIO_Label
PE6.GPIO_Label=PDN
PE6.Signal=GPIO_Output
PH0-OSC_IN\ (PH0).Mode=HSE-External-Clock-Source
PH0-OSC_IN\ (PH0).Signal=RCC_OSC_IN
RCC.HSE_VALUE=50000000
RCC.SYSCLKFreq_VALUE=480000000
RCC.SYSCLKSource=RCC_SYSCLKSOURCE_PLLCLK
board=custom

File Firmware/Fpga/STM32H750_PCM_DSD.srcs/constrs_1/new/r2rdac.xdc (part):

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set_property PACKAGE_PIN T5 [get_ports Clock_SI]
set_property PACKAGE_PIN N5 [get_ports Clock_SI_50MHZ]
set_property PACKAGE_PIN E2 [get_ports COAX_IN_FPGA]
set_property PACKAGE_PIN G17 [get_ports DSD_A]
set_property PACKAGE_PIN G18 [get_ports DSD_A_N]
set_property PACKAGE_PIN J17 [get_ports DSD_B]
set_property PACKAGE_PIN J18 [get_ports DSD_B_N]
set_property PACKAGE_PIN F18 [get_ports DSD_CLK]
set_property PACKAGE_PIN H17 [get_ports DSD_EN]
set_property PACKAGE_PIN L5 [get_ports DSP_SEL]
set_property PACKAGE_PIN B2 [get_ports HDMI_DATA]
set_property PACKAGE_PIN A1 [get_ports HDMI_FCLK]
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set_property PACKAGE_PIN T18 [get_ports I2S_FPGA_LRCLK]
set_property PACKAGE_PIN B17 [get_ports L_BCLK]
set_property PACKAGE_PIN B18 [get_ports L_CLK]
set_property PACKAGE_PIN C17 [get_ports L_DATA_N]
set_property PACKAGE_PIN A18 [get_ports L_DATA_P]
set_property PACKAGE_PIN V16 [get_ports LED1]
set_property PACKAGE_PIN U16 [get_ports LED2]
set_property PACKAGE_PIN V17 [get_ports LED3]
set_property PACKAGE_PIN R13 [get_ports MUTE]
set_property PACKAGE_PIN E1 [get_ports OPTICAL_IN_1]
set_property PACKAGE_PIN C1 [get_ports OPTICAL_IN_2]
set_property PACKAGE_PIN D18 [get_ports R_BCLK]
set_property PACKAGE_PIN E17 [get_ports R_CLK]
set_property PACKAGE_PIN E18 [get_ports R_DATA_N]
set_property PACKAGE_PIN D17 [get_ports R_DATA_P]
set_property PACKAGE_PIN R10 [get_ports RCLK_ON]
set_property PACKAGE_PIN G1 [get_ports SPDIF_CLK]
set_property PACKAGE_PIN H1 [get_ports SPDIF_DATA]
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set_property PACKAGE_PIN R16 [get_ports RASPI_SPI_MISO]
set_property PACKAGE_PIN P18 [get_ports RASPI_SPI_MOSI]

set_property PACKAGE_PIN A13 [get_ports DSD_EN_RL]

set_property DRIVE 4 [get_ports R_BCLK]
set_property DRIVE 4 [get_ports R_CLK]
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
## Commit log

2026-01-10 Add firmware and hardware
2026-04-07 DoP added
    DSD DoP added
2026-04-07 VHDL Code opt
    Clean bug and optimized
2026-04-07 DSD board added
    Added DSD board
2026-04-08 remove unused files
2026-04-09 DSD Board Rev
2026-04-09 Changing Hardware file structure
2026-04-10 add pictures
2026-04-13 add new pictures
2026-04-19 Fixed DSD play
    Fixed DSD play FPGA cross connection and XMOS and STM32H750 DSD Play
2026-04-19 some PCB/schemtic improvements
    some PCB improvements,
    three additional debug LEDs,
    add serial res. at data/clk line
2026-04-19 DAC Source Sellect Bug Fixed
